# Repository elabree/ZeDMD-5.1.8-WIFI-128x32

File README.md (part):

# The Arcade — powered by ZeDMD (WiFi Fork, 128×32, ESP32-S3-N16R8)

> 🇩🇪 **Deutschsprachige Anleitung:** [LIESMICH.md](LIESMICH.md)

**The Arcade** is an ESP32-S3 firmware for a 128×32 HUB75 LED matrix — a multifunctional smart display for clock, weather, GIFs, and internet radio. It has nothing to do with pinball.

- **Clock + weather** — live data from your own weather station via MQTT (WeeWx), with Open-Meteo as automatic fallback; configurable field names, visual fallback indicator
- **GIF screensaver** — animated GIFs from SD card, sorted alphabetically or shuffled, with optional synchronised MP3 audio per GIF
- **Webradio** — internet radio via I2S amplifier (MAX98357A); station logos, track title, equaliser, L/R swap
- **Web UI** — full configuration and control from any browser on your local network; no app, no account, no cloud
- **Batocera/Recalbox streaming** — receives animated game marquees via the ZeDMD protocol when a retro gaming frontend is running; the display switches automatically and returns to its normal mode afterwards

---

> 📝 *This README is a personal project diary rather than a complete guide. It documents what worked for me — your setup may differ. No claim to completeness; errors and omissions are possible.*

---

> **This started as a personal hobby fork of [PPUC/ZeDMD](https://github.com/PPUC/ZeDMD) v5.1.8**
> and has since grown well beyond it — the clock, weather, and webradio features are original
> work built on top, not part of upstream ZeDMD. What *is* inherited from upstream is the core
> DMD protocol handling and the HUB75 display driver — that foundation is why this project
> stays under the same GPLv2-or-later license as ZeDMD itself, and why it remains listed as a
> GitHub fork of it rather than a standalone repo.
> It is shared with the community in the hope that it might be useful — but it comes with **absolutely no support, no warranty, and no guarantee of any kind**.
> Issues and pull requests may not be responded to. Emails and messages regarding this project will likely go unanswered — not out of disrespect, but simply because this is a spare-time project maintained by one person.
> **Use entirely at your own risk.**

---

> ⚠️ **Panel size: only tested with 128×32 (2× chained 64×32 tiles).** The codebase already
> has build environments for larger panels (`256x64` / `S3-N16R8_256x64`, via `ZEDMD_HD`) and
> the core DMD rendering scales automatically with `TOTAL_WIDTH`/`TOTAL_HEIGHT` — but this has
> **not been built or tested**. The weather overlay and GIF screensaver have hardcoded pixel
> positions sized for 128×32 that would need adapting first.
>
> If you do try a larger panel: pay **significantly more attention to power supply sizing**
> than you would for 128×32. A single 64×32 HUB75 tile can draw up to ~25W (5V/5A) at full
> white; going to 256×64 roughly **quadruples the pixel count** versus this project's default
> 128×32 setup, and current draw scales accordingly. Undersized power supplies on large HUB75
> chains cause voltage drop, ghosting/dimming artifacts, and in the worst case connector or
> wiring damage — plan for adequate power injection points along the chain, not just a single
> feed at one corner.

---

https://github.com/jens-b/The-Arcade/raw/main/docs/images/ZeDMD_WiFi_128x32_demo.mp4

---

### Screenshots

| Clock + Weather | Weather Forecast | GIF Screensaver |
|:-:|:-:|:-:|
|  |  |  |

**Webradio — station name and logo on the display:**

**Internals / Back panel:**

| Inside | Back panel |
|:-:|:-:|
|  |  |

---

## 🆕 What's new in this release

### v1.9.0 *(this release)*

#### RSS News Ticker (Mode 7)
A new screensaver mode fetches headlines from any RSS 2.0 feed and scrolls them across the display. The feed URL is configurable in the web UI — presets for Tagesschau, BBC and others are built in, or enter any custom feed URL. Headlines refresh every 15 minutes. The ticker also appears as a slot in the GIF screensaver rotation (modes 0/2/4) and in the clock+weather rotation (modes 1/3).

#### Stock / Crypto / Index Ticker (Mode 8)
A new screensaver mode fetches live prices from Yahoo Finance (no API key required) and displays them as a carousel — one symbol at a time, cycling every few seconds. Supports stocks (`AAPL`, `SAP.DE`), crypto (`BTC-EUR`, `ETH-EUR`) and indices (`^DAX`, `^GSPC`). Up to 10 symbols, configurable in the web UI. Price and percentage change shown in green (positive) or red (negative). A mini sparkline shows the intraday trend. Refresh interval configurable (15 / 30 / 60 min). The ticker carousel also integrates into the GIF and clock modes — a symbol is shown between GIFs or at regular intervals.

#### WKN and ISIN support
German securities can now be entered as WKN (6-character alphanumeric, e.g. `DBX1ME`) or ISIN (12-character, e.g. `DE000DBX1ME3`) instead of ticker symbol. The firmware resolves the identifier to the correct Yahoo Finance symbol automatically on first fetch and caches the result.

#### Brownout protection
If the display resets due to a low-power event (e.g. a power bank running out), it now shows "Low power — sleeping 60s" and enters deep sleep for 60 seconds instead of immediately rebooting. This breaks the rapid reboot–draw–reboot cycle that drains a marginal power supply completely.

---

### v1.8.0

#### Clock digit drop animation
When a minute changes, each affected digit now animates: the old digit slides out downward while the new one drops in from above. Five frames at 40 ms each give a smooth 200 ms transition without impacting the normal display refresh rate.

#### Modes 1 and 2 — clock + weather combined
Modes 1 and 2 previously showed the clock alone. They now display the **clock and weather side by side** in the same layout as mode 3/4, removing the need for a separate weather-only mode slot and giving all time-based modes access to live weather data.

#### Webradio — automatic stream fallback
If a station stream is consistently slow (below the bitrate threshold for multiple consecutive checks), the firmware automatically searches [radio-browser.info](https://www.radio-browser.info) for an alternative URL for the same station and switches to it silently. The display shows the station name as before. A manual fallback can also be triggered via the radio page.

#### GIF screensaver — search by name
The screensaver file list now supports **live search by filename**. Type any substring into the search box and the list filters instantly on the backend — no page reload needed. Works across the full SD card library, even with thousands of files.

#### Configurable OpenMeteo timezone
The timezone used for the Open-Meteo weather API is now configurable in the admin panel (IANA format, e.g. `Europe/Berlin`). Previously hardcoded. The setting is saved to LittleFS and survives reboots. Only relevant if your coordinates are outside Central European time.

#### HTTPS radio streams
The mbedTLS SSL buffer has been moved to PSRAM, making HTTPS radio streams reliable. Previously, the SSL handshake frequently failed under memory pressure. Encrypted streams (`https://`) now work as well as plain HTTP.

#### GIF PSRAM pre-load + 50 fps minimum
GIF frames are now pre-loaded into PSRAM before rendering begins, eliminating mid-playback SD card stalls. A minimum floor of 50 fps is enforced — files with missing or zero frame-delay metadata now play at a sensible speed instead of running as fast as the CPU allows.

---

### v1.7.0

#### Critical stability fixes — watchdog now actively monitors the main task
A fundamental issue was present since the first WiFi firmware build: `enableLoopWDT()` was never called, meaning the Task Watchdog Timer (TWDT) never actually monitored the main loop task. All `esp_task_wdt_reset()` calls across the codebase were silent no-ops — the device relied only on the secondary IDLE-task starvation mechanism to detect hangs.

With `enableLoopWDT()` now correctly placed at the start of `setup()`, the TWDT actively monitors the loop task against the 5-second budget. This exposed three real hang points that are now fixed:

- **Large screensaver cache** — `TryLoadFolderCache()` reading 3 700+ lines without any watchdog reset caused a reboot loop on devices with many files. Fixed with a reset every 50 lines.
- **SoftAP countdown** — the 19-second WiFi-failure countdown ran without a single reset. Fixed.
- **NTP sync** — `clockInit()` calls `getLocalTime()` with a 5-second timeout, landing exactly on the WDT boundary. A reset is now issued before the call.

Devices that were showing repeated `TASK_WDT` reboot entries in `/diag` after upgrading from a previous firmware version should recover immediately with this release.

#### "The Arcade" startup logo
The boot logo has been updated from the generic PPUC logo to **The Arcade** branding. The crash-screen overlay was also corrected (it previously overwrote the logo during a first-boot crash sequence).

#### Radio icon reload fix
The **Reload Icons** action (`/icons_reload`) now also refreshes the radio icon slug cache. Previously, a newly uploaded station logo only appeared after a full reboot.

#### `/upload_asset` endpoint
A new endpoint accepts any PNG or RAW file and stores it directly in the LittleFS root. Useful for uploading custom boot logos or background assets without a full LittleFS flash.

#### Brightness save respects the display blank timer
Saving brightness via `/save_brightness` previously called `SetBrightness()` directly, which deactivated an active display-blank interval. It now goes through `ApplyBrightness()` and leaves the blank state untouched.

---

### v1.6.0

#### Weather icons — 17×17 pixel art, stored in LittleFS
The main weather icon (top-right of the clock/weather view) has been redrawn at **17×17** instead of 16×16. The odd size places the center on an exact pixel (8, 8) rather than between pixels — sun rays, moon crescent tips and fog lines are now perfectly symmetrical. Specific improvements per icon:

- **Sun** — cardinal rays narrowed to 1 px, lengthened to 3 px; diagonal rays extended toward the body for a more connected look
- **Moon** — wider crescent tips at top and bottom (3 px); crescent ends look rounded rather than pointed
- **Cloud bitmap** — extended from `uint16_t` (16 cols) to `uint32_t` (17 cols); all cloud-based icons benefit
- **Fog** — sixth stripe added at the bottom to fill the extra row
- **Rain / Drizzle / Showers** — drop positions adjusted for equal horizontal spacing

The 11 weather icons are now stored as **RGBA files in LittleFS** (`/icons_weather/`) instead of being hardcoded in the firmware. This means:
- Icons can be **replaced without reflashing** — upload new ones via `/upload_icon_weather`
- The icon set is consistent with the existing system (`/icons/` for emoji, `/icons_radio/` for station logos)
- First-time setup: upload the 11 `weather_*.rgba` files from `data/icons_weather/` after the initial flash

#### Temperature display — tighter minus sign
The minus sign for negative temperatures now **kerns closer to the digit**: for single-digit negatives (`−1` to `−9`) the minus is positioned where the tens digit would be; for two-digit negatives (`−10` to `−19`) it moves 2 px closer to the leading `1`. The result is a more natural, compact look on the 128×32 display.

#### Interactive weather location map
The **Weather (Open-Meteo)** section in `admin.html` now shows a **Leaflet / OpenStreetMap** map. Click anywhere on the map or drag the marker to set your coordinates — no manual lat/lon entry needed. City search is also available. The map initialises at the currently saved coordinates.

#### HUB75 library 3.0.14 + Line Decoder parameter
The ESP32-HUB75-MatrixPanel-DMA library has been updated from **3.0.12 to 3.0.14**. A new **Line Decoder** parameter is now exposed in the Panel section of the admin page — required for panels that use a shift-register-based row decoder instead of direct addressing (rare, but necessary for certain panel types). Default value is 0 (no effect on standard panels). Setting is saved to LittleFS and survives reboots.

#### Removed unused SDMMC build environment
The `S3-N16R8_128x32_wifi_sdmmc_webradio` PlatformIO environment has been removed from `platformio.ini`. It was not actively maintained and only added noise to the build configuration. The standard SPI SD build (`wifi_sd_webradio`) remains the only supported target.

#### 7-segment display styles
Four segment style presets are available under the **Display Settings** section of the web UI:

- **Default** — chamfered corners with junction clearing (original look)
- **Classic** — inner notch at segment junctions; chamfered inner corners
- **Classic 2** — early-build look: L-junction inner pixel + inner chamfer, "0" exempt
- **Modern** — plain rectangular segments, no chamfering

The active style is saved to LittleFS and survives reboots.

#### Glow effect *(beta)*
A **Glow β** button in Display Settings toggles a drop-shadow effect on the clock digits (2 px offset, 30 % brightness). Experimental — not persisted across reboots.

#### Equalizer range extended to ±12 dB
The Bass / Mid / Treble sliders now go from **−12 dB to +12 dB** (previously ±6 dB). Useful for speakers like the FRS8 where cutting bass and boosting treble significantly improves perceived audio clarity.

#### SD card firmware update
Place a `firmware.bin` in the `/UPDATE/` folder on the SD card — on the next boot it is flashed automatically and the file is deleted. A manual trigger button is also available on the **Admin** page for updating without a reboot.

---

### v1.5.3

#### Configurable MQTT field names
The JSON field names used to read weather data from your MQTT broker are now configurable in the admin panel — no reflash required. This matters if your WeeWx (or other weather station) uses non-standard field names. Default values match the standard WeeWx LOOP output: `outTemp_C`, `outHumidity`, `windSpeed_kph`, `barometer_mbar`. Settings are saved to LittleFS and survive reboots.

#### Visual fallback indicator for OpenMeteo data
When MQTT has been silent for more than 10 minutes, the weather display switches to Open-Meteo data as a fallback. All four weather values (temperature, humidity, wind, pressure) are now shown in **grey** instead of white during this fallback period — an immediate visual cue that the data is not coming from your local weather station. After 30 minutes without MQTT, the existing orange **"MQTT fehlt"** text appears as before.

#### Unknown weather code fallback icon
If Open-Meteo returns a WMO weather code that has no matching icon, the display now shows the **question mark icon** (`question.rgba` from the icon set) instead of the misleading cloudy icon that was used before. In practice this should never appear — all codes used by Open-Meteo are handled — but it makes the system more robust.

---

### v1.5.2

#### Tabbed Web UI
The main page has been reorganised into three tabs — **Screensaver**, **Display** and **Radio** — making it much easier to navigate on both desktop and mobile. SD card & storage info plus the Admin button remain always visible above the tabs.

#### Display Timer *(scheduled display off)*
Set a daily on/off schedule for the LED matrix — useful for automatically turning the display off at night. Configure From/Until times under the **Display** tab. A **"Display off / Display on"** button lets you instantly turn the display off and on without changing the timer settings.

#### Stereo / Mono toggle
The **Radio** tab now shows separate **Stereo** and **Mono** buttons next to the volume slider. Switch the audio output to mono without a firmware rebuild — useful if you only have one speaker connected or experience phase issues.

#### Station logos on the LED matrix
When a radio station starts playing, the matching station logo (if uploaded) is shown on the LED matrix alongside the station name and track title.

#### Boot text improvements
Status messages during boot ("booting", "loading...", "SD OK", "LittleFS OK") are now shown at the bottom-left of the display so they no longer overlap the boot logo.

#### Rescan buttons
A **Rescan** button appears in the screensaver file list and the GIF audio file list after an upload — or can be triggered manually at any time. Rescans the SD card and LittleFS without a reboot and updates the file list immediately.

#### SD card SPI speed — up to 40 MHz
On a proper PCB layout (no Dupont wires), the SD card is now initialised at 40 MHz first, with an automatic fallback chain (40 → 25 → 20 → 8 MHz). Previously the maximum was 8 MHz. Faster initialisation and file access, especially noticeable during GIF and audio scans.

#### Equalizer
A three-band **equaliser (Bass / Mid / Treble)** is now available in the **Radio** tab. Settings are saved to LittleFS and survive reboots and station switches.

#### Weather icons — further improvements
The 8×8 forecast icons (3-day view) have been completely redrawn. Three new icons added: drizzle, showers and snow now have their own symbols — previously they shared a generic rain icon. Total: 11 distinct weather icons.

#### L/R channel swap
If your left and right speakers are physically wired the wrong way around, a single **L/R Swap** button in the **Radio** tab swaps the audio channels in software — no rewiring needed. Settings survive reboots.

#### Custom branding
The boot screen and web UI header now show the **The Arcade** logo instead of the generic ZeDMD logo. The PPUC splash screen has been removed.

---

### v1.5.1

#### Weather Icons — native 16×16 pixel art
All 8 weather icons have been redrawn as native 16×16 pixel art — sharper and more detailed than the scaled-up 8×8 bitmaps used before. Each icon has a unique hand-crafted color gradient: sun with rays, crescent moon, cloud, rain drops, snow, lightning bolt, and partly-cloudy variants. The smaller 8×8 icons used in the 3-day forecast were further improved in v1.5.2.

#### SD Card — more robust initialisation
The SD card now retries with progressively slower SPI speeds (8 → 4 → 2 MHz, up to 6 attempts) before giving up. Previously a single failed mount attempt would mark the SD as unavailable for the entire session. This resolves intermittent boot failures with marginally connected or slow-to-mount SD cards.

#### Bug Fixes
- Emoji text: cursor position 0 was treated as falsy in JavaScript — the cursor is now correctly preserved when inserting an emoji at the very start of the input field
- Icon upload: interrupted uploads no longer leave orphaned `.tmp` files on LittleFS
- Icon folder scan: directory handle no longer leaks when a non-directory entry is encountered

---

### v1.5 and earlier

### Webradio
Stream internet radio stations directly through the ZeDMD's built-in speaker.
Requires a **MAX98357A I2S amplifier module** — see wiring below.

- Dedicated station manager at `/radio.html` — search stations via [radio-browser.info](https://www.radio-browser.info), save presets with logo icons
- **Country quick-select buttons** (🇩🇪 DE / 🇦🇹 AT / 🇨🇭 CH / 🇳🇱 NL / 🇫🇷 FR) load the top-100 stations for that country in one tap; Niedersachsen regional filter still available
- Station name, track title and station logo displayed in the web UI
- Volume control via slider on the main page and the radio page
- Station name and track title scroll on the LED matrix for 5 seconds when a station starts, then returns to the screensaver — tap "DMD 10s" to show it again
- Presets survive firmware updates (stored in LittleFS)
- Stable station switching — no more audio dropout on channel change
- Stream URLs from radio-browser.info are automatically normalised (removes `?ti=` playlist hints that caused the audio library to hang)
- **L/R channel swap** — if your left and right speakers are physically wired the wrong way around, a single button in the **Radio** tab swaps the audio channels in software — no rewiring needed

> **Technical note — audio library patch:** The L/R swap feature required modifying the `ESP32-audioI2S` library internally, because it does not provide this function out of the box. Rather than changing the library files by hand (which would be lost on every library update), a build-time patch script (`scripts/patch_audio_lib.py`) injects the change automatically on each compile. This script was developed with the help of **[Claude Code](https://claude.ai/code)** (AI coding assistant by Anthropic) — pinpointing the exact location inside the audio pipeline where samples could be swapped safely, and making the patch idempotent (safe to run repeatedly). I would not have attempted this alone.

> **⚠️ Weather API:** Open-Meteo is accessed via HTTP instead of HTTPS. TLS handshakes consistently caused memory-related crashes in the web radio build. Since Open-Meteo provides public data without requiring a login, HTTPS is not necessary here.

### GIF Preview in the browser
Click any GIF filename in the screensaver file list or the "currently shown" field to open a live animated preview directly in the browser — without touching the display. Favourite, ignore and play controls are available inside the preview.

> **Note:** Opening a GIF preview while webradio is playing may cause brief audio stuttering — SD card access and audio streaming share the same CPU core. This is a known limitation.

### GIF Audio
Play a matching MP3 file from the SD card in sync with an animated GIF screensaver. The filename must match the GIF (e.g. `demo.gif` → `demo.mp3`). Upload audio files via the main page or drop them in `/GifAudio/` on the SD card directly.

- File list is cached in LittleFS — after the first boot scan, subsequent reboots load instantly (same mechanism as the screensaver file cache)
- Paginated file list in the web UI with previous/next buttons (20 files per page)
- Scan can be aborted via the **"Cancel Scan"** button that appears after an upload

> ⚠️ **First-boot scan time:** Depending on how many files are in `/GifAudio/`, the initial scan over SPI can take a very long time. Progress is shown on the display ("GifAudio XXXX"). After the scan the list is cached in LittleFS — every subsequent reboot loads in seconds.

> **Note:** GIF audio plays once per GIF cycle — looping is not yet implemented.

### SDMMC Board Support *(not actively maintained)*
Added support for boards with an **onboard SD card via SDMMC interface** (1-bit mode) — no external SPI module required. See pin table below for the required HUB75 cable changes.

> **Note:** This build variant is not actively maintained. Development focus is on the standard SPI SD build (`wifi_sd_webradio`). The SDMMC variant may work but is not tested with each release.

### GIF Screensaver Order
- **A-Z toggle** — switch between alphabetical and random playback order directly on the main page
- **Reshuffle button** — re-randomise the GIF order at any time without a full reload

### Configurable Timezone
The NTP clock timezone can now be set directly on the admin page — no firmware rebuild required.
A dropdown covers the most common zones (Central Europe, UK, UTC, US East/Central/Mountain/Pacific); a **Custom** option accepts any POSIX timezone string for full flexibility. The setting is stored in LittleFS and survives reboots.

### SD Card Mount / Eject
The main page now shows a **Mount / Eject** toggle button next to the SD card status bar.
- **⏏ Eject** (grey) — safely unmounts the SD card so it can be removed while the device stays powered
- **⏻ Mount** (green) — remounts the card after reinsertion; updates the screensaver file list and GIF audio cache automatically

### Stability & Bug Fixes
This release includes a comprehensive overhaul of memory management and task safety:

- **Admin page no longer crashes** — root cause identified via coredump analysis: lwIP assertion in AsyncTCP 3.3.5 triggered by the Basic Auth handshake. Fixed by updating AsyncTCP to 3.4.10
- Fixed race condition on station switching — audio no longer reverts to the previous station
- Weather data (MQTT + HTTP) now safely synchronized between CPU cores
- SD card directory listing moved out of network callbacks — no more audio stuttering during web access
- Weather HTTP response buffered in PSRAM — eliminates large internal SRAM spike during fetch
- All file uploads are now atomic (`.tmp` + rename) — interrupted uploads no longer leave corrupt files
- `screensaverFiles` array protected by mutex against concurrent web access
- Audio task priority raised above the web server task — reduces stream dropouts under concurrent web traffic

---

## 🧪 Experimental Features

> These features are functional but still being polished. Use at your own risk and expect rough edges.

---

### Batocera WiFi streaming

By default, Batocera's DMD server only streams to a single USB-connected DMD. To stream to a WiFi ZeDMD at the same time, a second `dmdserver` instance needs to be set up manually.

A full step-by-step guide — including dual-DMD marquee control, attract/playing modes, and troubleshooting — is available here:

📄 **[docs/batocera-dual-dmd.md](docs/batocera-dual-dmd.md)** (EN) | **[docs/batocera-dual-dmd-DE.md](docs/batocera-dual-dmd-DE.md)** (DE)

> ⚠️ Tested with Batocera **v42**. Batocera **>v42** may have introduced changes that break this setup. Verify carefully before updating Batocera.

---

### Batocera game start/stop trigger

`scripts/batocera_game_start.sh` and `scripts/batocera_game_stop.sh` trigger GIF audio playback on ZeDMD when a game starts or stops on Batocera. The DMD itself continues to receive live frames from the emulator as usual — these scripts only control the audio layer.

> ⚠️ Not yet fully tested end-to-end — the `/gif_audio_play` endpoint works, but the Batocera-side trigger has not been verified in a real game session.

**How it works:**
- On game start: Batocera sends the ROM name to ZeDMD → ZeDMD plays the matching MP3 from `/GifAudio/` on the SD card
- On game stop: ZeDMD stops audio playback
- Naming convention: ROM filename without extension → `medieval_madness.zip` → `medieval_madness.mp3`

**Setup:**
1. Open both scripts and set `IP_ZEDMD` to your ZeDMD's fixed IP address
2. Copy to Batocera:
   ```bash
   scp scripts/batocera_game_start.sh root@batocera.local:/userdata/system/scripts/gameStart.sh
   scp scripts/batocera_game_stop.sh root@batocera.local:/userdata/system/scripts/gameStop.sh
   ```
3. Place matching MP3 files on the SD card under `/GifAudio/`

> ⚠️ **If a `gameStart.sh` already exists on Batocera** (e.g. from another project), do **not** replace it — append the `curl` call from the script to the existing file instead.

---

### Batocera audio extraction script

`scripts/extract_gif_audio.sh` extracts the first N seconds of audio from Batocera scraped game videos and saves them as MP3 files ready for ZeDMD.

> ⚠️ Tested on Batocera only. Requires `ffmpeg` and `python3` available on the Batocera system.

**Prerequisites:**
- Batocera with SSH access
- `ffmpeg` installed on Batocera (check: `which ffmpeg`)
- `python3` installed on Batocera (check: `which python3`)
- Scraped game videos in `gamelist.xml` (`/userdata/roms/<system>/`)

**Usage (run via SSH on Batocera):**
```bash
ssh root@batocera.local "bash /tmp/extract_gif_audio.sh [options]"
```

| Option | Default | Description |
|--------|---------|-------------|
| `--system` | `mame` | ROM system folder name |
| `--limit` | `10` | Max number of files to extract |
| `--duration` | `15` | Clip length in seconds |
| `--out` | `/userdata/zedmd/gif_audio` | Output directory |
| `--game` | *(all)* | Filter by partial game name |

**Workflow:**
1. Copy the script to Batocera: `scp scripts/extract_gif_audio.sh root@batocera.local:/tmp/`
2. Run it via SSH (see above)
3. Open the output folder in Finder: **Network → batocera → share → zedmd → gif_audio**
4. Upload the MP3 files via **`http://<ZeDMD-IP>/`** → GIF-Audio section

---

### Display Text

Send a custom text message to the LED matrix directly from the web UI.

- Static or scrolling display — short texts are shown centered, longer texts scroll automatically
- Color picker for free RGB color selection
- Configurable display duration (5–60 seconds)
- Instantly interrupts any running screensaver or GIF and restores it afterwards
- **Emoji picker** — 34 emojis (❤️ ⭐ 🔥 😊 🎉 and more) rendered as pixel-art icons directly in the scrolling text; icons are stored as RGBA files in LittleFS (`/icons/`)

---

### Stereo Audio

Stereo output using **two MAX98357A modules** — one for the left channel, one for the right.

The SD pin is a voltage-level channel-select strap. The values below were measured and confirmed to work with MAX98357A breakout boards that already have a **1 MΩ resistor from SD to Vin** onboard. If your board has a different onboard resistor, these values will not apply — always check your board's schematic and measure before connecting.

* **Module L (Left Channel):** Connect a **100 kΩ** resistor from SD to VCC **(5V)**.
* **Module R (Right Channel):** Connect a **390 kΩ** resistor from SD to VCC **(5V)**.

The ESP32-audioI2S library outputs stereo I2S natively when playing stereo source files. Each module automatically decodes its designated channel based on the SD pin voltage.

| MAX98357A Pin | ESP32-S3 | Notes |
|---------------|----------|-------|
| BCLK | **GPIO 9** | shared — both modules |
| LRC (WSEL) | **GPIO 14** | shared — both modules |
| DIN | **GPIO 21** | shared — both modules |
| SD — Module L | **100 kΩ to VCC** | → **Left channel** |
| SD — Module R | **390 kΩ to VCC** | → **Right channel** |
| VIN | **5V** *(recommended)* | each module separately |
| GND | **GND** | each module separately |

> ⚠️ The resistor values above are verified at **5V only**. For 3.3V supply the right-channel value changes to approx. **210 kΩ** (untested). 3.3V supply is **not recommended** — it increases distortion and loads the 3.3V rail.

> ⚠️ **DISCLAIMER:**
> These resistor values were determined experimentally with a specific MAX98357A breakout board variant that has a 1 MΩ onboard resistor from SD to Vin. Other board variants may require different values. **Always consult the MAX98357A datasheet, check your board's actual schematic, and measure voltages before connecting.**
> **Use entirely at your own risk — no warranty or liability of any kind.**

---

## Hardware

### Custom PCB by [elabree](https://github.com/elabree) ✅
A dedicated carrier board designed and built by [elabree](https://github.com/elabree) — tested and confirmed working with this firmware. The board hosts the ESP32-S3-DevKitC-1-N16R8, an SD card module socket, and two MAX98357A stereo amplifier sockets on a single clean PCB.

Two revisions are available:
- **Rev1.1** — for original Espressif ESP32-S3-DevKitC (0.9″ pin row spacing)
- **Rev1.2** — for most clone boards (1″ pin row spacing)

KiCad sources and Gerber files for ordering at JLCPCB: [KiCad/ZeDMD_WiFi/](https://github.com/jens-b/The-Arcade/tree/main/KiCad/ZeDMD_WiFi) (included in this repository).

A big thank-you to elabree for designing and contributing this board to the project — this would not have happened without his work.

---

## 🔜 Planned Features

### Code cleanup *(on my list)*
The code has grown organically and is honestly a bit messy in places — I know. I'm planning to clean things up at some point, but no promises on when. It works, which counts for something.

---

## What's different from original ZeDMD

This fork is **WiFi-only** and targets the **ESP32-S3-N16R8** with a **128×32 LED matrix**.

### All added features

- **WiFi OTA firmware update** — flash new firmware directly via browser (`/admin.html`); firmware version with build ID and branch shown on admin page (format: `5.1.8-jb (date) [abc1234@main]`)
- **Screensaver** — GIF/RAW slideshow with clock and weather display (Open-Meteo, plain HTTP for RAM efficiency)
- **Screensaver management** — favorites, ignore list, alphabetical/random order, strict timer, pause/resume
- **GIF Preview** — click any filename to open an animated browser preview; favorite/ignore/play controls inside the preview
- **GIF Audio** — play a matching MP3 from `/GifAudio/` on the SD card in sync with the screensaver GIF; `scripts/extract_gif_audio.sh` extracts audio from Batocera video files
- **Improved web interface** — file management, per-file favorite/ignore buttons, pagination with wrap-around
- **Admin page** — WiFi, display, transport, MQTT, weather settings
- **Webradio** — internet radio via I2S amplifier (MAX98357A); station search via [radio-browser.info](https://www.radio-browser.info); preset management with logo icons; LED matrix shows station info for 5 s on start, "DMD 10s" button for on-demand display
- **Config Export/Import** — full configuration backup and restore via browser (`/config_transfer.html`)
- **Display Text** — send custom text with emojis to the LED matrix via the web UI; static or scrolling with color selection and configurable duration (5–60 s); 34 emojis available via built-in picker
- **LittleFS icon system** — three icon folders: `/icons/` (20×20 emoji/question), `/icons_weather/` (17×17 weather icons, uploadable via `/upload_icon_weather`), `/icons_radio/` (32×32 station logos); splash assets via `/upload_asset`
- **Display Timer** — schedule daily on/off times for the LED matrix (e.g. off at 23:00, on at 07:00); "Display off / Display on" button for instant manual control
- **Tabbed web UI** — main page organised into Screensaver / Display / Radio tabs; SD card & admin always visible
- **Stereo Audio** *(experimental)* — two MAX98357A modules for true stereo output; channel selection via SD-pin resistor strapping (5V only, values verified); Stereo/Mono toggle in the web UI
- **RSS News Ticker (Mode 7)** — fetches headlines from any RSS 2.0 feed and scrolls them across the display; feed URL configurable in the web UI (presets included); headlines refresh every 15 min; also shown as a carousel slot in GIF screensaver (modes 0/2/4) and clock+weather modes (1/3)
- **Stock / Crypto / Index Ticker (Mode 8)** — live prices from Yahoo Finance (no API key required); supports stocks (`AAPL`, `SAP.DE`), crypto (`BTC-EUR`), and indices (`^DAX`, `^GSPC`); up to 10 symbols; price and percentage change in green/red; mini sparkline for intraday trend; refresh interval 15/30/60 min; carousel integrates into GIF and clock modes
- **WKN and ISIN support** — German securities can be entered as WKN (6-char alphanumeric, e.g. `DBX1ME`) or ISIN (12-char, e.g. `DE000DBX1ME3`); automatically resolved to Yahoo Finance symbol and cached
- **Brownout protection** — low-power reset shows "Low power — sleeping 60s" and deep-sleeps for 60 seconds instead of looping; prevents power drain with marginal supplies (e.g. power banks)

---

## Hardware — ESP32-S3-N16R8 Note

### 💡 Power supply

The ZeDMD can draw a noticeable amount of current — especially when bright GIFs are displayed, webradio is streaming, and WiFi is active all at once. A laptop USB port or a basic phone charger may not deliver enough stable power for this, which can lead to unexpected reboots or an unstable display.

**If things seem unreliable: use a decent 5V / 2A USB power adapter** (the kind that comes with a good phone or tablet). How much power is actually needed varies quite a bit depending on the content — dark GIFs with no audio use much less than a bright screensaver at full volume.

---

### 🧠 On the verge of a nervous breakdown — what this little chip is actually doing

At any given moment, the ESP32-S3 in this build is simultaneously:

- driving a 128×32 HUB75 LED matrix over DMA
- serving a full web UI with live updates over WiFi
- streaming and decoding webradio (MP3/AAC) over I2S in a dedicated FreeRTOS task
- reading and playing animated GIFs from an SD card
- playing matching MP3 files in sync with those GIFs
- fetching live weather data and rendering icons
- handling MQTT, OTA, file uploads, and a paginated file browser for 2 000+ files
- maintaining a LittleFS cache, crash logs, and boot diagnostics

All of this on a chip with **327 KB of internal SRAM** — of which the WiFi stack, TCP server, and audio buffers claim most at runtime, leaving sometimes less than **1 KB free** at peak load. The 8 MB PSRAM handles the large caches and pixel buffers, but anything touching WiFi or TCP must live in internal SRAM — and that is genuinely tight.

The firmware works hard to keep things stable: PSRAM-backed caches, careful buffer sizing, staggered HTTP requests, and a heap monitor that logs free memory every 30 seconds. But this is a device running at the edge of what its hardware class was designed for — and it shows, in the best possible way.

---

### ⚠️ Missing 5V on VIN pin (IN-OUT solder bridge)

Some ESP32-S3-N16R8 boards do not provide 5V on the VIN pin out of the box.
If your ZeDMD powers up but the LED matrix stays dark or behaves unexpectedly, check the **IN-OUT solder bridge** near the 5V/GND pins.

**Fix:** Close the IN-OUT bridge with a small solder blob to route 5V from USB to the VIN pin.

> ⚠️ Modifying hardware is at your own risk!

For other known hardware issues and general ZeDMD documentation see the **[original ZeDMD README](https://github.com/PPUC/ZeDMD#readme)**.

---

## SD Card

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
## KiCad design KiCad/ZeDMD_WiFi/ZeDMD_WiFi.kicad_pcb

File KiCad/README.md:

# ZeDMD_WiFi PCB
This is a carrier board for the ESP32-S3-DevKitC-1-N16R8 with the following features:
- ZeDMD compatible HUB75 connector for RGB Matrix Panels and 4 push-buttons
- 5V terminal block with 2 different use cases:
  - Output for the RGB panels, using +5V power from USB-C
  - 5V input for the DevKit, in case the RGB panels are on an external supply (jumper on J6)
- A socket (J2) for a Micro SD Card module. Note that this module needs to have a 5V - 3.3V regulator. Always check that the pinout of your module corresponds to the [schematics diagram](ZeDMD_WiFi/docs/ZeDMD_WiFi.pdf)
- Two sockets (J1 and J3) for MAX98357A amplifier modules (Adafruit i2s class-d mono-amp). The modules are on the +5V supply (Devkit USB-C 5V, USB-C breakout Vin1 and Vin2).
- Two sockets (J8 and J5) for USB-C breakout boards to serve as +5V inputs. VBUS1 and VBUS2 drive the +5V supply via an "ideal diode" LM66200 module at J13. 

## Power budget
The power supply voltage is +5V.

### USB-C limitation
The maximum current USB-C can deliver at 5V is 3A (Pmax = 15W). It does not matter that a USB-C PD port is able to deliver more power because that means using a higher voltage. This is not possible with this design!

### RGB matrix panel
Two 64x32 RGB matrix panels draw 5A (25W) at 100% intensity. Since these panels are designed for daylight operation, this intensity is really high. Usually no more than 50% is needed (2.5A, 12.5W). This leaves sufficient power (0.5A; 2.5W) for the DevKit and SD card.

### MAX98357A modules
The amplifier modules use 5V supply voltage. The maximum required current depends on impedance of the connected speakers. If there is insufficient power avalable, the supply may dip during loud sounds causing clipping at the output. This may damage the speakers.

#### Power needs for 2 MAX98357A modules:
| Vin | Rspeaker | Pout_max |    Iin (Pin)  |
| --- | -------- | -------- | ------------- |
| 5V  | 8 ohm    | 1.8 W    | 0.9 A (4.5 W) |
| 5V  | 4 ohm    | 3.2 W    | 1.6 A (8 W)   |

### Power supply Recommendations
1. If USB-C is the preferred way to power everything: Then it is best to use a USB-C breakout (J5 or J8) to power the RGB matrix panel via J7; Do not place a jumper on J6.
2. The best alternative is a 5V/5A (25W) Meanwell switchmode power supply (SMPS). Connect the RGB matrix panels directly to the SMPS. Options to power the PCB including Devkit:
- USB-C (Devkit OR Breakout at J5 and/or J8); A 25W SMPS is needed.
- SMPS (Place jumper on J6 and connect the SMPS +5Vout to J7; Use a 40W SMPS.
*Note that option 2 allows full brighness of the RGB panels*

## Options
The general recommendation is: only mount the parts you will be using. So, if you don't need speaker outputs, don't mount the amplifier modules. If you don't use the push buttons, there is no need to mount them.

### RGBout at J7
Diode D2 will cause a voltage drop of 0.7 V to reduce voltage at the panels. The main reason is that some RGB panels do not work correctly at 5V. If the RGB panels work correctly at 5V, a wire bridge can be used instead of the diode.

### 5Vin at J7
As explained a jumper (or wire bridge) at J6 is only needed in absence of USB-C power. In that case J7 becomes the 5V input.

### MAX98357A gain
J10 and J11 can be used to select the amplifier gain. The default gain is 9dB if nothing is connected. For 12dB place a jumper or wire bridge. A 100k resistor can be placed for even more gain (15dB).
*Note that this only adjusts the volume, it will not increase the maximum output power.* TP2 and TP3 are connected to Vin. These testpoints are normally not needed. But these can be used to decrease the gain if needed...

## More information
[Licensed under the TAPR Open Hardware License (www.tapr.org/OHL)](LICENSE.txt)

[info](ZeDMD_WiFi/docs)

## Gerber and Drill files for PCB ordering
1. The Espressif ESP32-S3-DevKitC has 0.9" distance between rows: [production_Rev1.1.zip](/KiCad/ZeDMD_WiFi/production_Rev1.1.zip)
2. Most clones have 1" distance between rows: [production_Rev1.2.zip](/KiCad/ZeDMD_WiFi/production_Rev1.2.zip)
3. Simplified power supply selection. Additional USB-C +5V input. Added ADXL345 Accelerometer: [production_Rev1.3.zip](/KiCad/ZeDMD_WiFi/production_Rev1.3.zip)
Example [ordering information](ZeDMD_WiFi/docs/ZeDMD_WiFi_JLCPCB_ordering.png)

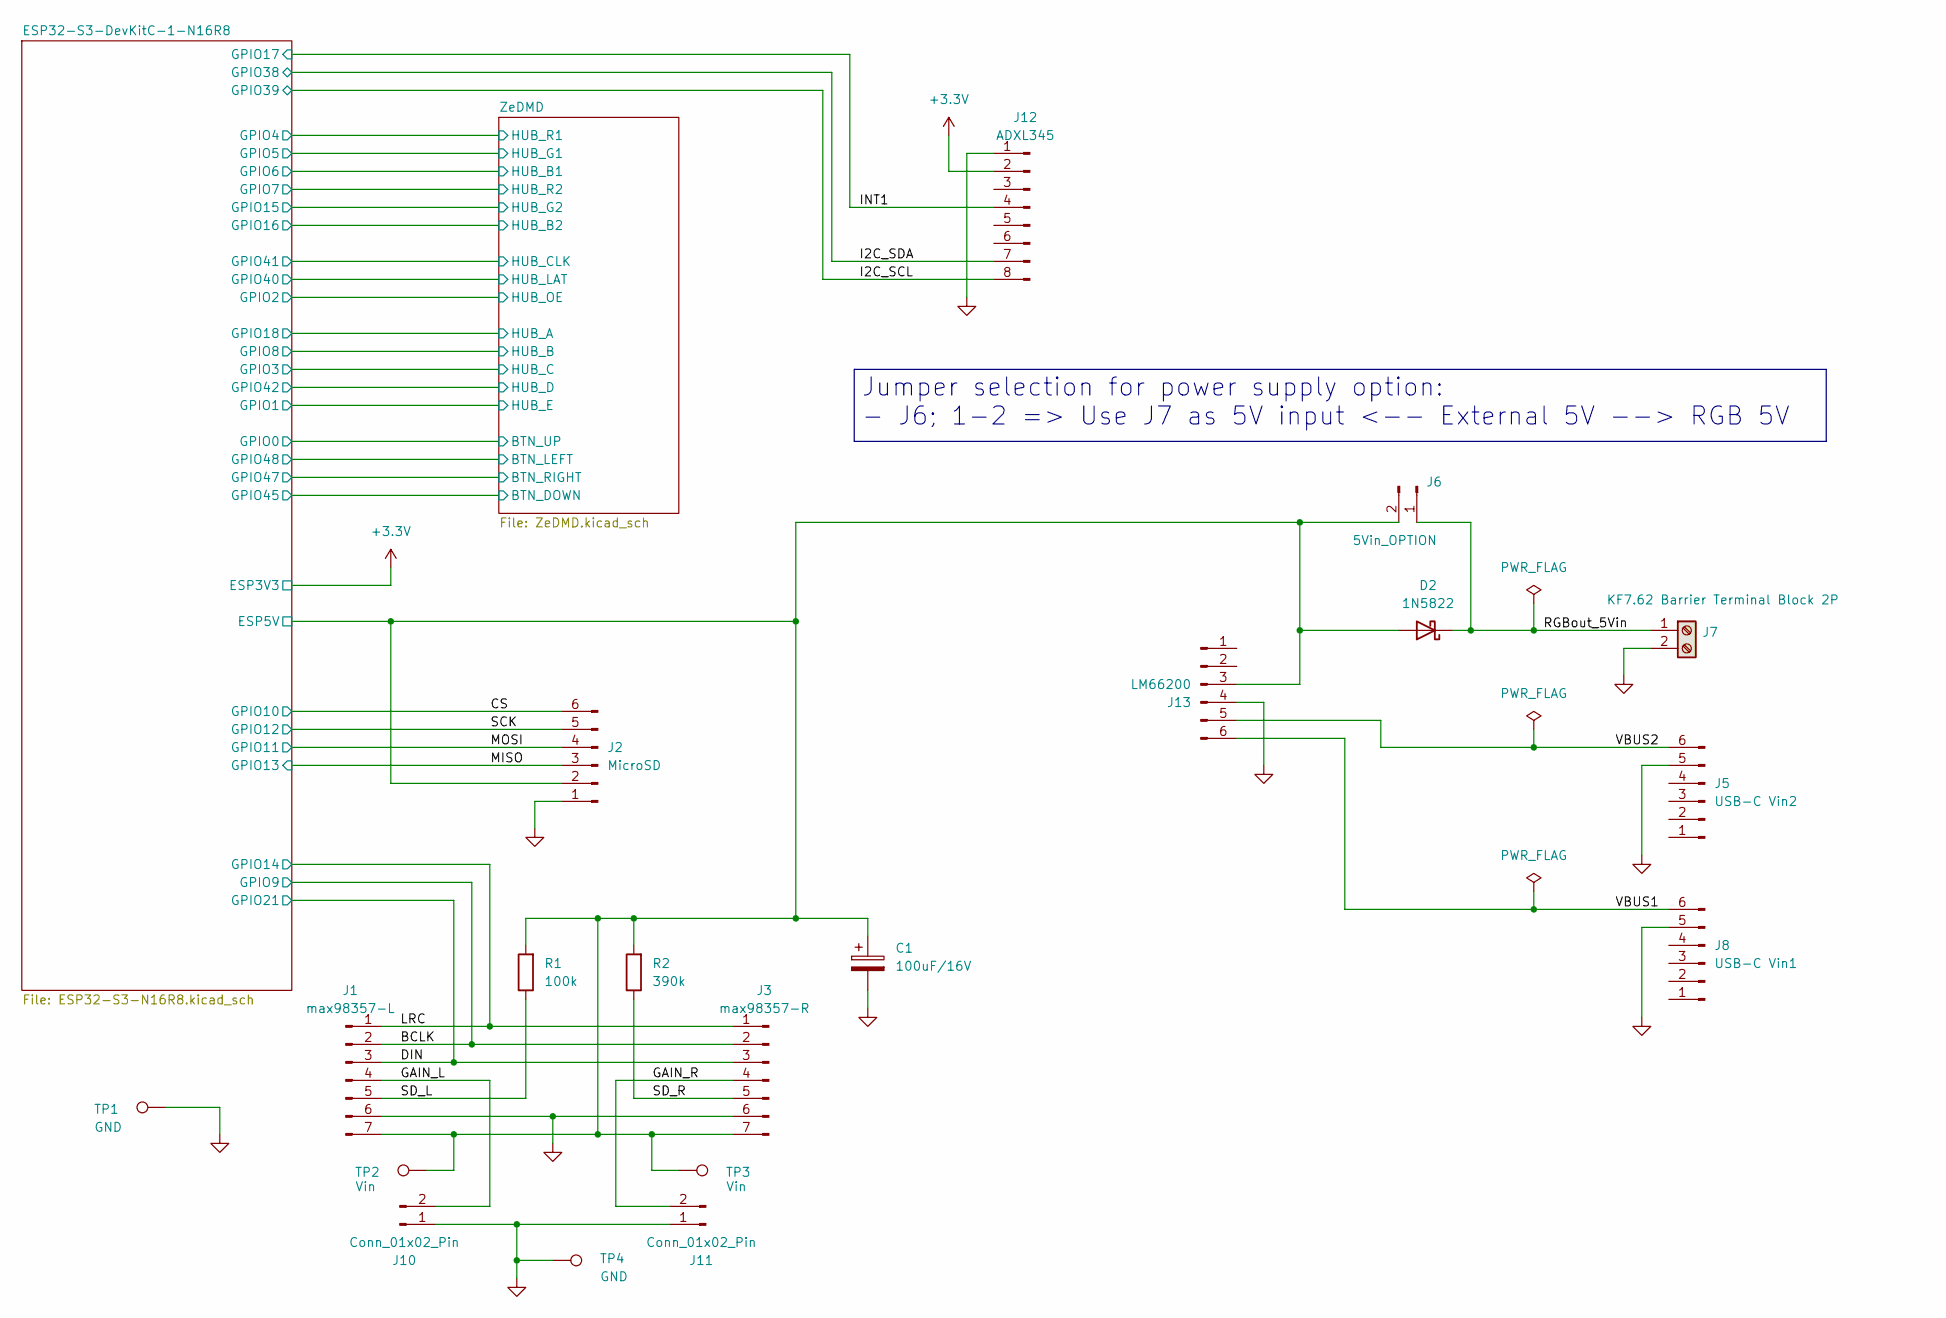
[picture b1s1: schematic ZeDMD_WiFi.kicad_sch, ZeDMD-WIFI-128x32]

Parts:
C1: 100uF/16V; CP_Radial_D8.0mm_P2.50mm
D2: 1N5822; D_DO-201AD_P15.24mm_Horizontal
J1: max98357-L; PinSocket_1x07_P2.54mm_Vertical
J2: MicroSD; PinSocket_1x06_P2.54mm_Vertical
J3: max98357-R; PinSocket_1x07_P2.54mm_Vertical
J5: USB-C Vin2; PinSocket_1x06_P2.54mm_Vertical
J6: 5Vin_OPTION; PinHeader_1x02_P2.54mm_Vertical
J7: KF7.62 Barrier Terminal Block 2P; KF7.62_2P; Voltage 5V
J8: USB-C Vin1; PinSocket_1x06_P2.54mm_Vertical
J10, J11: Conn_01x02_Pin; PinHeader_1x02_P2.54mm_Vertical
J12: ADXL345; PinHeader_1x08_P2.54mm_Vertical
J13: LM66200; PinSocket_1x06_P2.54mm_Vertical
R1: 100k; R_Axial_DIN0207_L6.3mm_D2.5mm_P10.16mm_Horizontal
R2: 390k; R_Axial_DIN0207_L6.3mm_D2.5mm_P10.16mm_Horizontal
TP1, TP4: GND; PinHeader_1x01_P2.54mm_Vertical
TP2, TP3: Vin; PinHeader_1x01_P2.54mm_Vertical

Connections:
+3.3V: J12.2; also elsewhere on the board
/BCLK: J1.2, J3.2; also elsewhere on the board
/CS: J2.6 (CS); also elsewhere on the board
/DIN: J1.3, J3.3; also elsewhere on the board
/ESP32-S3-DevKitC-1-N16R8/ESP5V: C1.1, D2.2 (A), J1.7, J2.2 (VCC), J3.7, J6.2, J13.3, R1.2, R2.2, TP2.1 (1_1), TP3.1 (1_1); also elsewhere on the board
/GAIN_L: J1.4, J10.2
/GAIN_R: J3.4, J11.2
/I2C_SCL: J12.8; also elsewhere on the board
/I2C_SDA: J12.7; also elsewhere on the board
/INT1: J12.4; also elsewhere on the board
/LRC: J1.1, J3.1; also elsewhere on the board
/MISO: J2.3 (MISO); also elsewhere on the board
/MOSI: J2.4 (MOSI); also elsewhere on the board
/RGBout_5Vin: D2.1 (K), J6.1, J7.1
/SCK: J2.5 (SCK); also elsewhere on the board
/SD_L: J1.5, R1.1
/SD_R: J3.5, R2.1
/VBUS1: J8.6, J13.6
/VBUS2: J5.6, J13.5
GND: C1.2, J1.6, J2.1 (GND), J3.6, J5.5, J7.2, J8.5, J10.1, J11.1, J12.1, J13.4, TP1.1 (1_1), TP4.1 (1_1); also elsewhere on the board

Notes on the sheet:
Jumper selection for power supply option: - J6; 1-2 => Use J7 as 5V input <-- External 5V --> RGB 5V

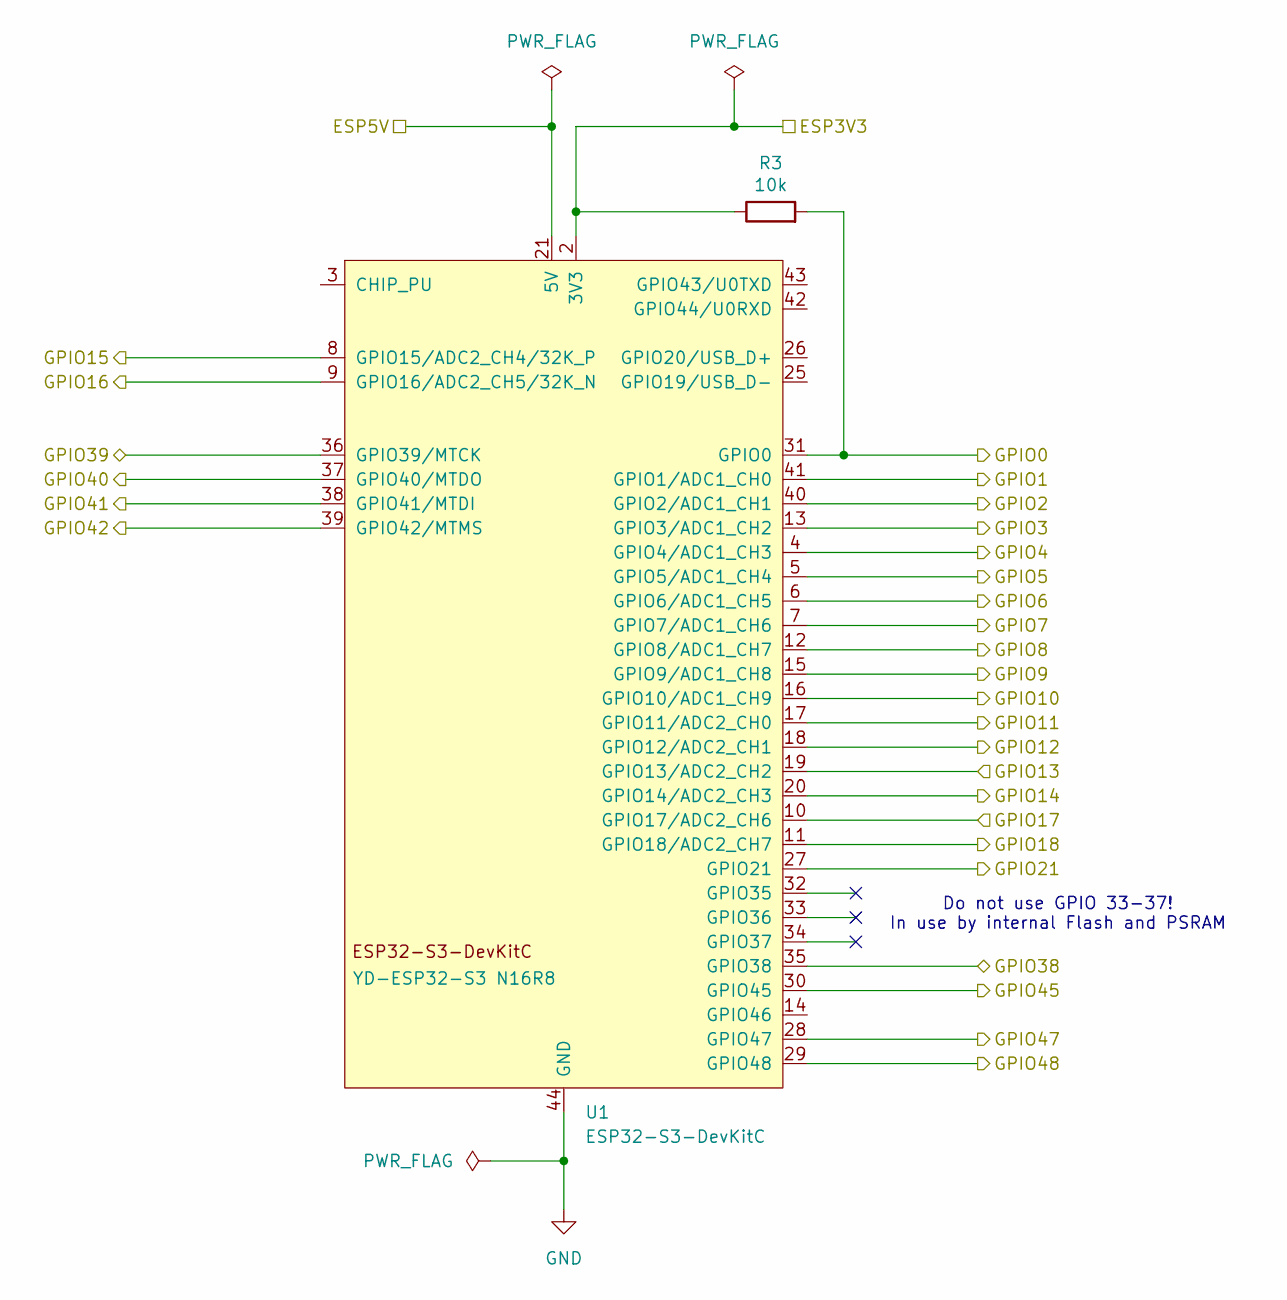
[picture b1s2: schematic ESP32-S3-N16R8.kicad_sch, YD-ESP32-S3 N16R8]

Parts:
R3: 10k; R_Axial_DIN0207_L6.3mm_D2.5mm_P10.16mm_Horizontal
U1: ESP32-S3-DevKitC

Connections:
+3.3V: R3.1, U1.1 (3V3), U1.2 (3V3); also elsewhere on the board
/BCLK: U1.15 (GPIO9/ADC1_CH8); also elsewhere on the board
/CS: U1.16 (GPIO10/ADC1_CH9); also elsewhere on the board
/DIN: U1.27 (GPIO21); also elsewhere on the board
/ESP32-S3-DevKitC-1-N16R8/ESP5V: U1.21 (5V); also elsewhere on the board
/I2C_SCL: U1.36 (GPIO39/MTCK); also elsewhere on the board
/I2C_SDA: U1.35 (GPIO38); also elsewhere on the board
/INT1: U1.10 (GPIO17/ADC2_CH6); also elsewhere on the board
/LRC: U1.20 (GPIO14/ADC2_CH3); also elsewhere on the board
/MISO: U1.19 (GPIO13/ADC2_CH2); also elsewhere on the board
/MOSI: U1.17 (GPIO11/ADC2_CH0); also elsewhere on the board
/SCK: U1.18 (GPIO12/ADC2_CH1); also elsewhere on the board
/ZeDMD/BTN_DOWN: U1.30 (GPIO45); also elsewhere on the board
/ZeDMD/BTN_LEFT: U1.29 (GPIO48); also elsewhere on the board
/ZeDMD/BTN_RIGHT: U1.28 (GPIO47); also elsewhere on the board
/ZeDMD/BTN_UP: R3.2, U1.31 (GPIO0); also elsewhere on the board
/ZeDMD/HUB_A: U1.11 (GPIO18/ADC2_CH7); also elsewhere on the board
/ZeDMD/HUB_B: U1.12 (GPIO8/ADC1_CH7); also elsewhere on the board
/ZeDMD/HUB_B1: U1.6 (GPIO6/ADC1_CH5); also elsewhere on the board
/ZeDMD/HUB_B2: U1.9 (GPIO16/ADC2_CH5/32K_N); also elsewhere on the board
/ZeDMD/HUB_C: U1.13 (GPIO3/ADC1_CH2); also elsewhere on the board
/ZeDMD/HUB_CLK: U1.38 (GPIO41/MTDI); also elsewhere on the board
/ZeDMD/HUB_D: U1.39 (GPIO42/MTMS); also elsewhere on the board
/ZeDMD/HUB_E: U1.41 (GPIO1/ADC1_CH0); also elsewhere on the board
/ZeDMD/HUB_G1: U1.5 (GPIO5/ADC1_CH4); also elsewhere on the board
/ZeDMD/HUB_G2: U1.8 (GPIO15/ADC2_CH4/32K_P); also elsewhere on the board
/ZeDMD/HUB_LAT: U1.37 (GPIO40/MTDO); also elsewhere on the board
/ZeDMD/HUB_OE: U1.40 (GPIO2/ADC1_CH1); also elsewhere on the board
/ZeDMD/HUB_R1: U1.4 (GPIO4/ADC1_CH3); also elsewhere on the board
/ZeDMD/HUB_R2: U1.7 (GPIO7/ADC1_CH6); also elsewhere on the board
GND: U1.22 (GND), U1.23 (GND), U1.24 (GND), U1.44 (GND); also elsewhere on the board

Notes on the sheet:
Do not use GPIO 33-37! In use by internal Flash and PSRAM

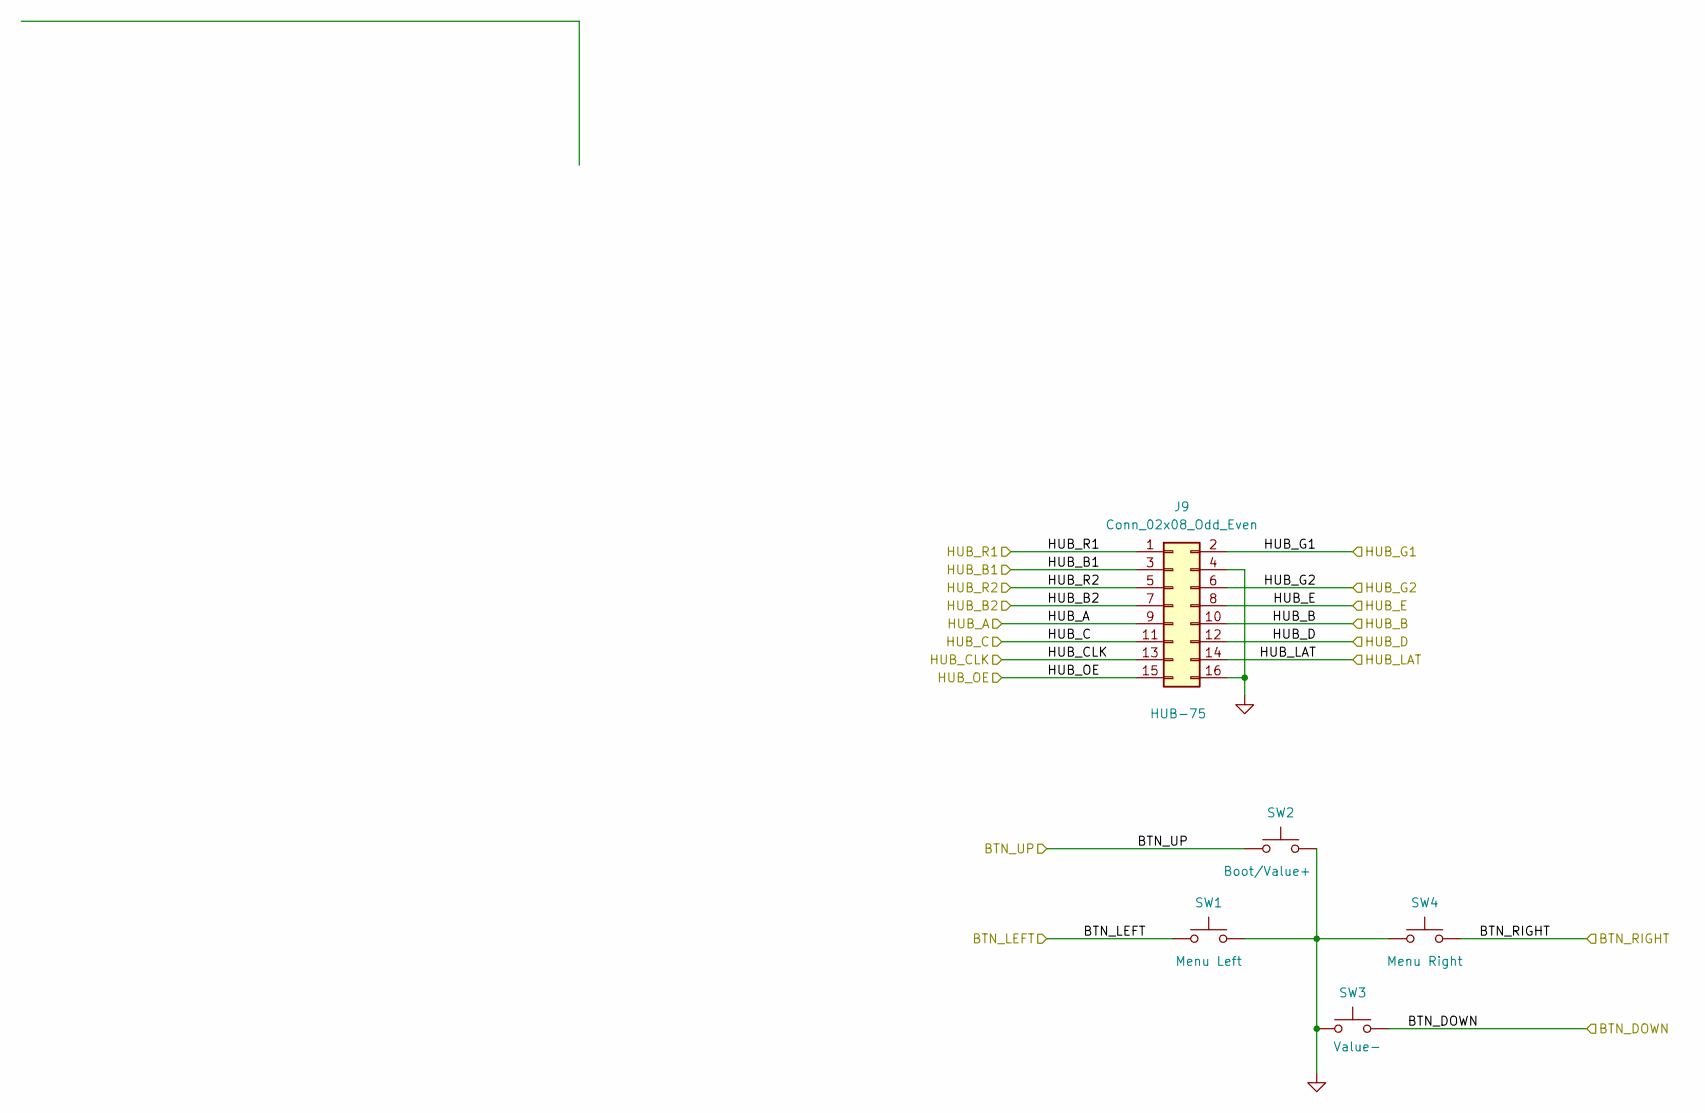
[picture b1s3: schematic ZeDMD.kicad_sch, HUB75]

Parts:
J9: Conn_02x08_Odd_Even; IDC-Header_2x08_P2.54mm_Vertical; JLCPCB Rotation Offset 270
SW1: Menu Left; SW_PUSH_6mm
SW2: Boot/Value+; SW_PUSH_6mm
SW3: Value-; SW_PUSH_6mm
SW4: Menu Right; SW_PUSH_6mm

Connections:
/ZeDMD/BTN_DOWN: SW3.1; also elsewhere on the board
/ZeDMD/BTN_LEFT: SW1.1; also elsewhere on the board
/ZeDMD/BTN_RIGHT: SW4.1; also elsewhere on the board
/ZeDMD/BTN_UP: SW2.1; also elsewhere on the board
/ZeDMD/HUB_A: J9.9; also elsewhere on the board
/ZeDMD/HUB_B: J9.10; also elsewhere on the board
/ZeDMD/HUB_B1: J9.3; also elsewhere on the board
/ZeDMD/HUB_B2: J9.7; also elsewhere on the board
/ZeDMD/HUB_C: J9.11; also elsewhere on the board
/ZeDMD/HUB_CLK: J9.13; also elsewhere on the board
/ZeDMD/HUB_D: J9.12; also elsewhere on the board
/ZeDMD/HUB_E: J9.8; also elsewhere on the board
/ZeDMD/HUB_G1: J9.2; also elsewhere on the board
/ZeDMD/HUB_G2: J9.6; also elsewhere on the board
/ZeDMD/HUB_LAT: J9.14; also elsewhere on the board
/ZeDMD/HUB_OE: J9.15; also elsewhere on the board
/ZeDMD/HUB_R1: J9.1; also elsewhere on the board
/ZeDMD/HUB_R2: J9.5; also elsewhere on the board
GND: J9.4, J9.16, SW1.2, SW2.2, SW3.2, SW4.2; also elsewhere on the board

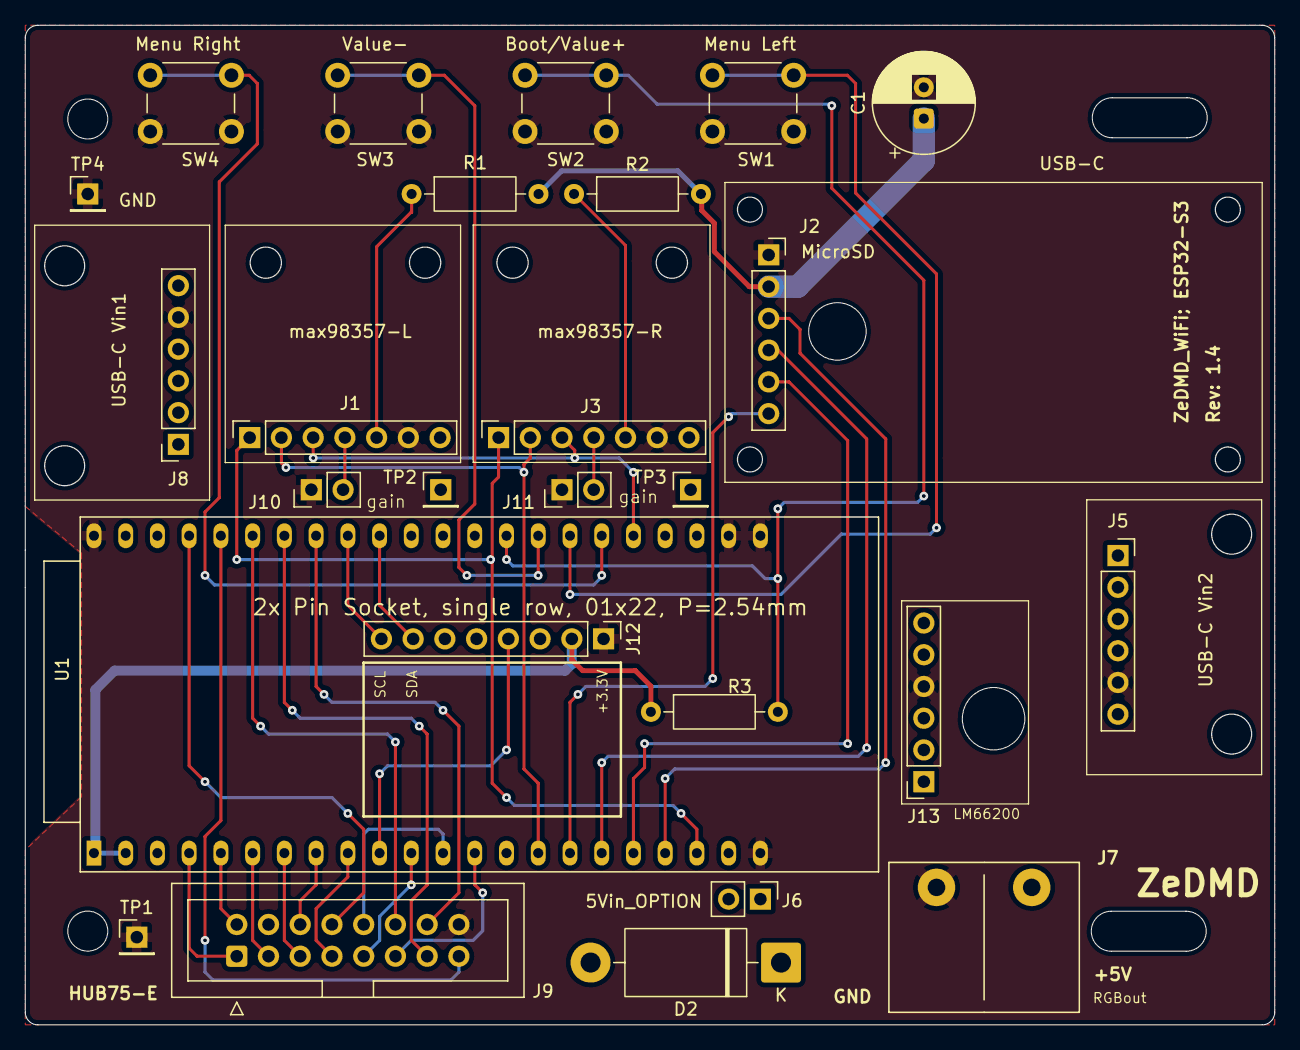
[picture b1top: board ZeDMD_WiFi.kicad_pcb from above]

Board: 4 copper layers, 100.0 x 80.0 mm, 26 parts (0 on the bottom side), 38 nets.

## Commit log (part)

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2026-06-03 Release: GIF preview, GIF audio, Webradio station manager and firmware stability
    - In-browser GIF preview with favorite, ignore and play controls
    - GIF audio: MP3 from /GifAudio/ plays in sync with screensaver
    - extract_gif_audio.sh: extracts audio from Batocera scraped videos (experimental)
    - radio.html: station search via radio-browser.info, presets with logo icons
    - LED matrix shows station info for 5 s on play; off by default; 10 s on demand
    - radio_status: mutex-protected snapshots, volatile radioCurrentPreset
2026-06-05 Fix & Improve: GIF-Audio, Radio-URL, Build-ID
    GIF-Audio (Verbesserungen):
    - LittleFS-Cache wie Screensaver — kein SD-Scan bei Neustart nach erstem Boot
    - Kein Re-Scan bei Seitenaufruf (war bereits für Screensaver gefixt, fehlte bei Audio)
    - cancelSdScan-Unterstützung
    - DMD-Fortschrittsanzeige und Log konsistent mit Screensaver
    - UI konsistent mit Screensaver-Dateiliste (Pagination, CSS)
2026-06-07 Empty project
2026-06-07 Initial setup
2026-06-12 Release v1.1: GIF-Audio, diagnostics, SD improvements, Batocera integration
    Features:
    - GIF-Audio: /gif_audio_play + /gif_audio_stop endpoints with fuzzy filename
    matching against PSRAM-cached file list; global on/off toggle; per-file
    preview button in UI
    - Diagnostics: boot statistics and reset reason counters via /diag endpoint;
    admin reset + log deletion
2026-06-12 Docs: Batocera Dual-DMD Anleitung auf Deutsch, alle Batocera-Abschnitte als experimentell, Warntext >v42
2026-06-18 Release v1.2: Webradio-Verbesserungen, Display Text, Heap-Fixes, Docs-Restrukturierung
    Webradio:
    - Manuelle URL-Eingabe in radio.html (Name + URL, Test + Speichern)
    - Bitrate in Suchergebnissen angezeigt
    Display Text (experimentell):
    - Beliebigen Text über Web-UI auf LED-Matrix senden
    - Statisch (zentriert) oder scrollend (automatisch bei langem Text)
2026-06-21 SchematicsV1.1
2026-06-21 Placement V1.1
2026-06-22 Schematics update and pngs added
2026-06-23 Release v1.4 — Timezone, SD Mount/Eject, radio.html UX, Upload-Verbesserungen
    Features:
    - Zeitzone auf Admin-Seite konfigurierbar — Dropdown mit Presets (DE/AT/CH, UK,
    UTC, US), Custom-Option für beliebige POSIX-Strings; gespeichert in LittleFS
    - SD-Karte per UI mounten und auswerfen — Mount/Eject-Toggle-Button auf der
    Hauptseite; remount mit Retry-Loop, aktualisiert Dateilisten automatisch
    - GIF-Upload zeigt Vorschau direkt nach dem Upload
2026-06-26 Placement ready
2026-06-27 Routing
2026-06-28 PCB updates and production files
2026-06-29 Release v1.5.1: 16×16 Wetter-Icons, SD-Init robuster, Emoji-Bugfixes
    Feature: Alle 8 Wetter-Icons als native 16×16 Pixel-Art neu gezeichnet
    — Sonne mit Strahlen, Mondsichel, Wolke, Regen, Schnee, Blitz, Mischbewölkt
    — Farbgradienten pro Icon; 8×8 Forecast-Icons unverändert
    Feature: Emoji-Lauftext mit 33 Pixel-Art-Icons (❤️ ⭐ 🔥 😊 🎉 …)
    — RGBA-Icons in LittleFS (/icons/ + /icons_small/)
    — Emoji-Picker im Web-UI
2026-06-29 Docs: elabree als GitHub-Link in Credits
2026-06-29 Docs: elabree-Link auch im Custom-PCB-Abschnitt
2026-06-30 Remove duplicate schematics

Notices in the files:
README.md:
Same as the original project — see [LICENSE](LICENSE).
This project is licensed under GPL v2 — commercial use is permitted under those terms.
